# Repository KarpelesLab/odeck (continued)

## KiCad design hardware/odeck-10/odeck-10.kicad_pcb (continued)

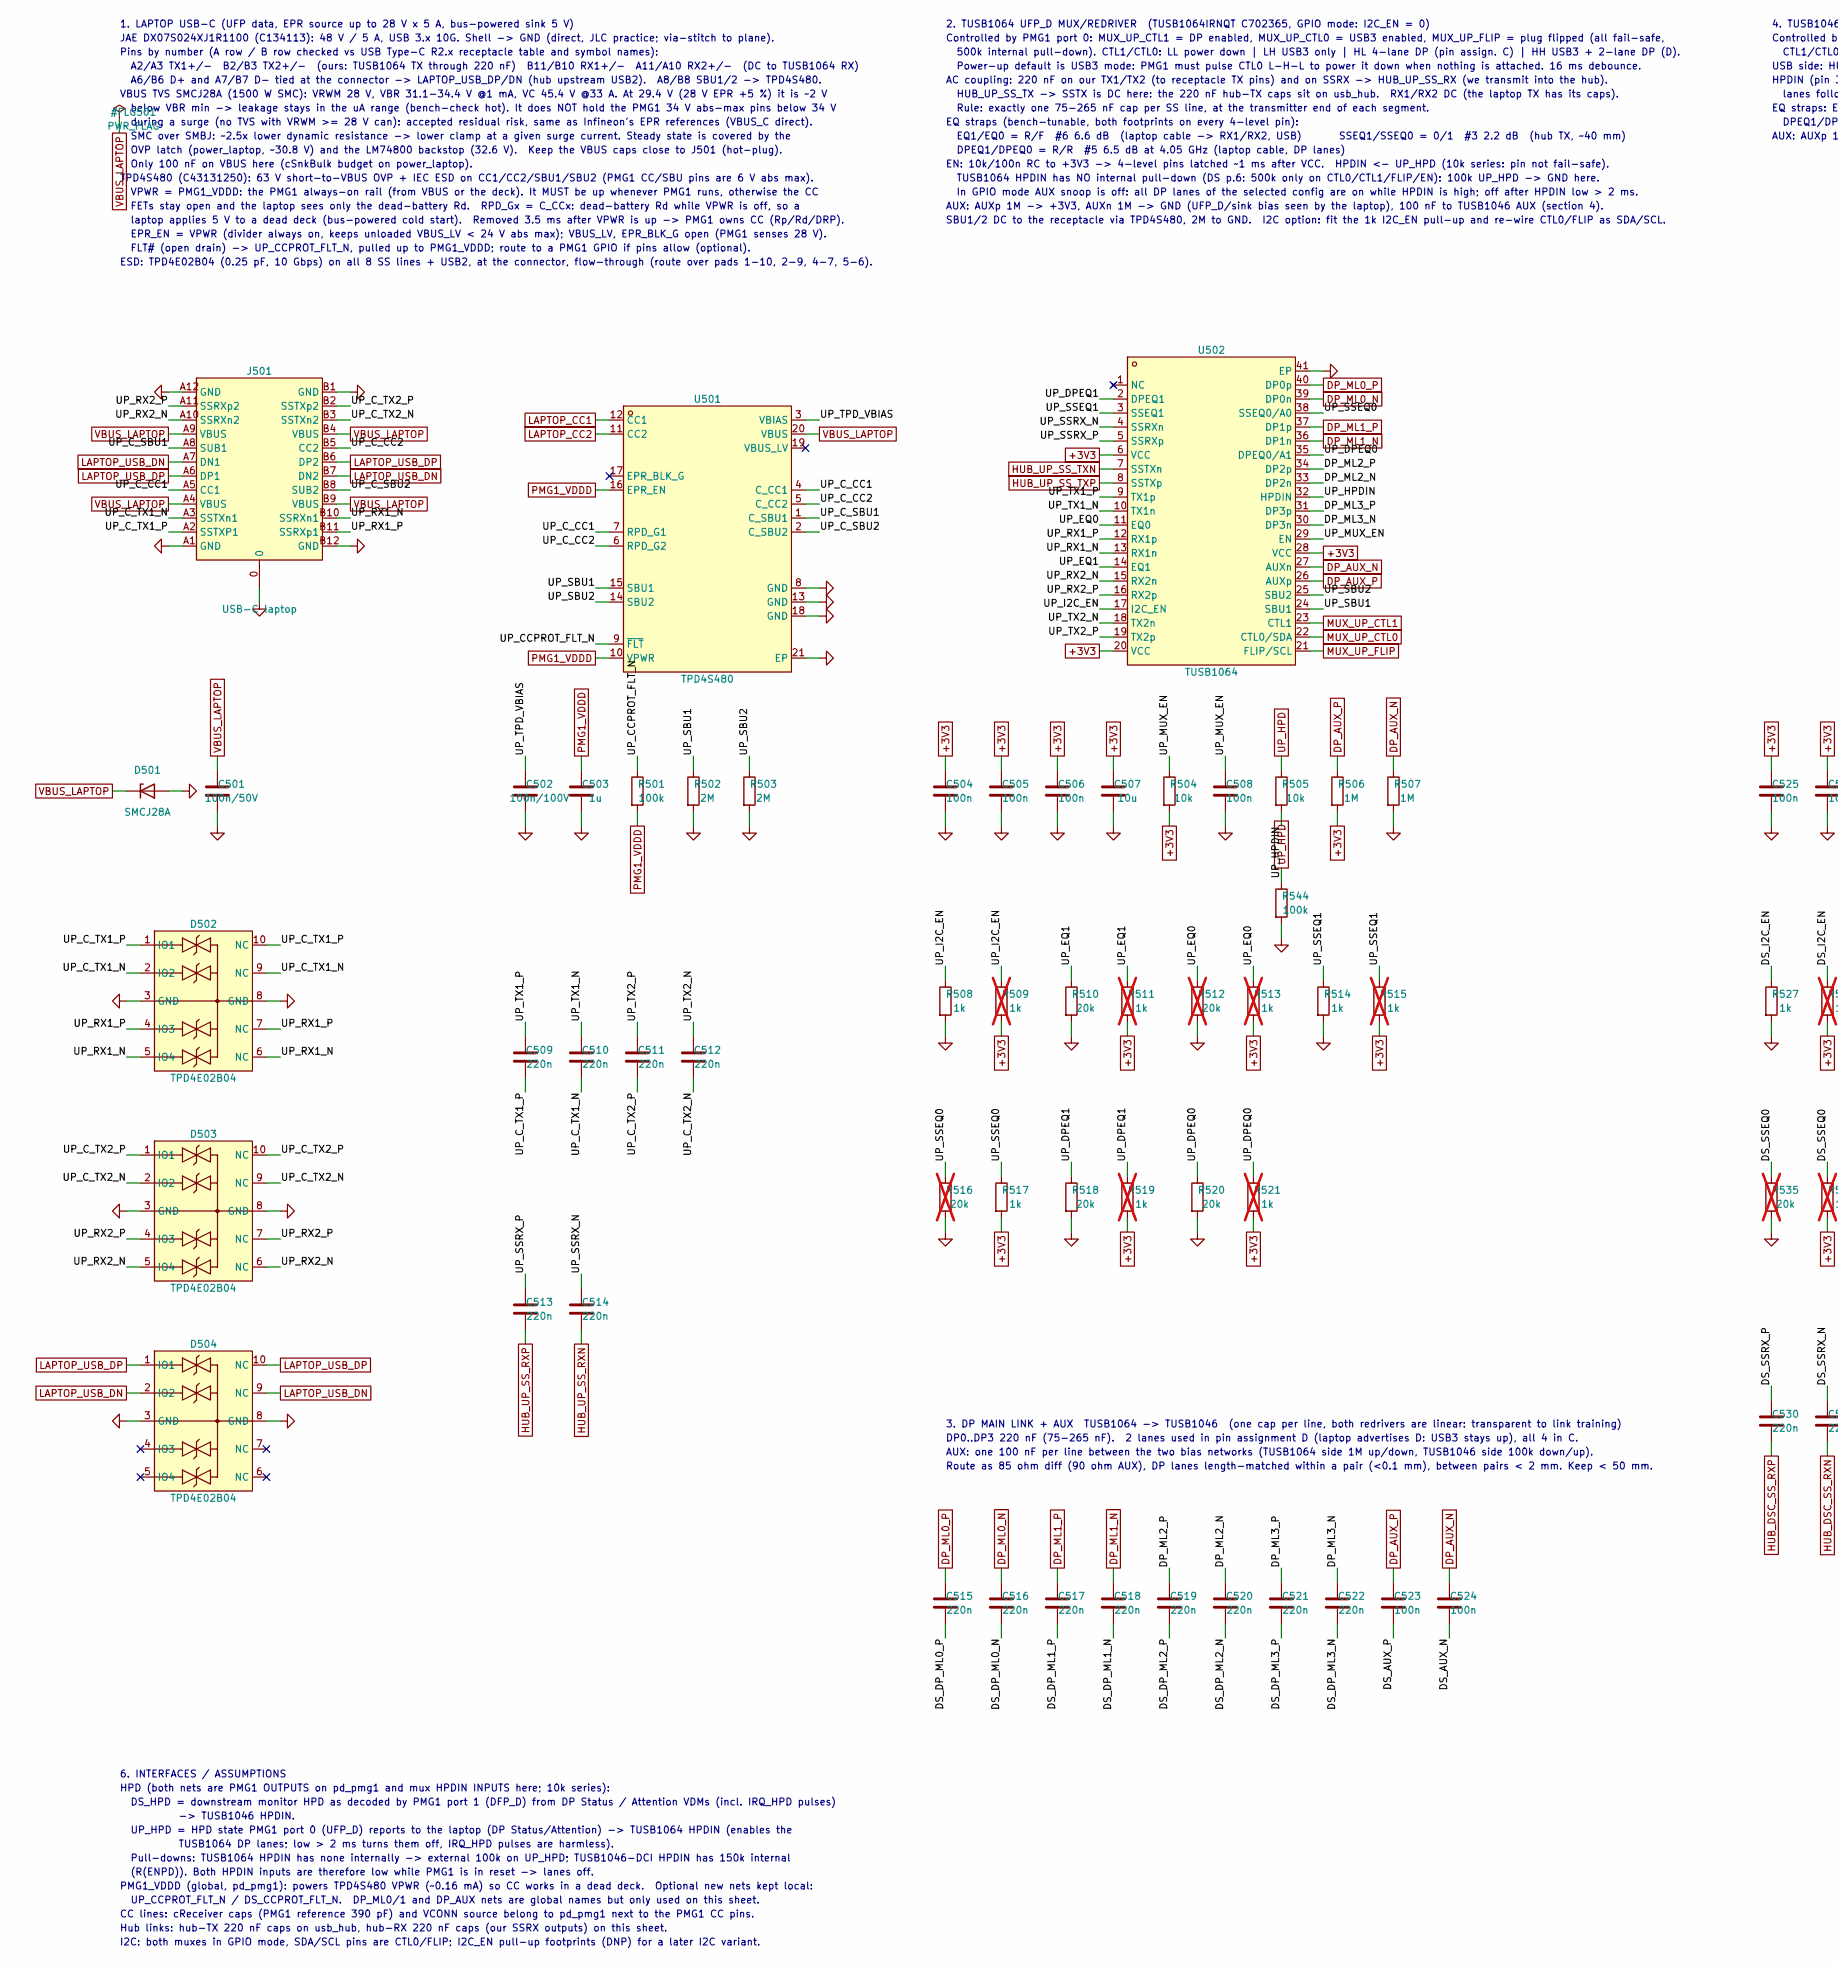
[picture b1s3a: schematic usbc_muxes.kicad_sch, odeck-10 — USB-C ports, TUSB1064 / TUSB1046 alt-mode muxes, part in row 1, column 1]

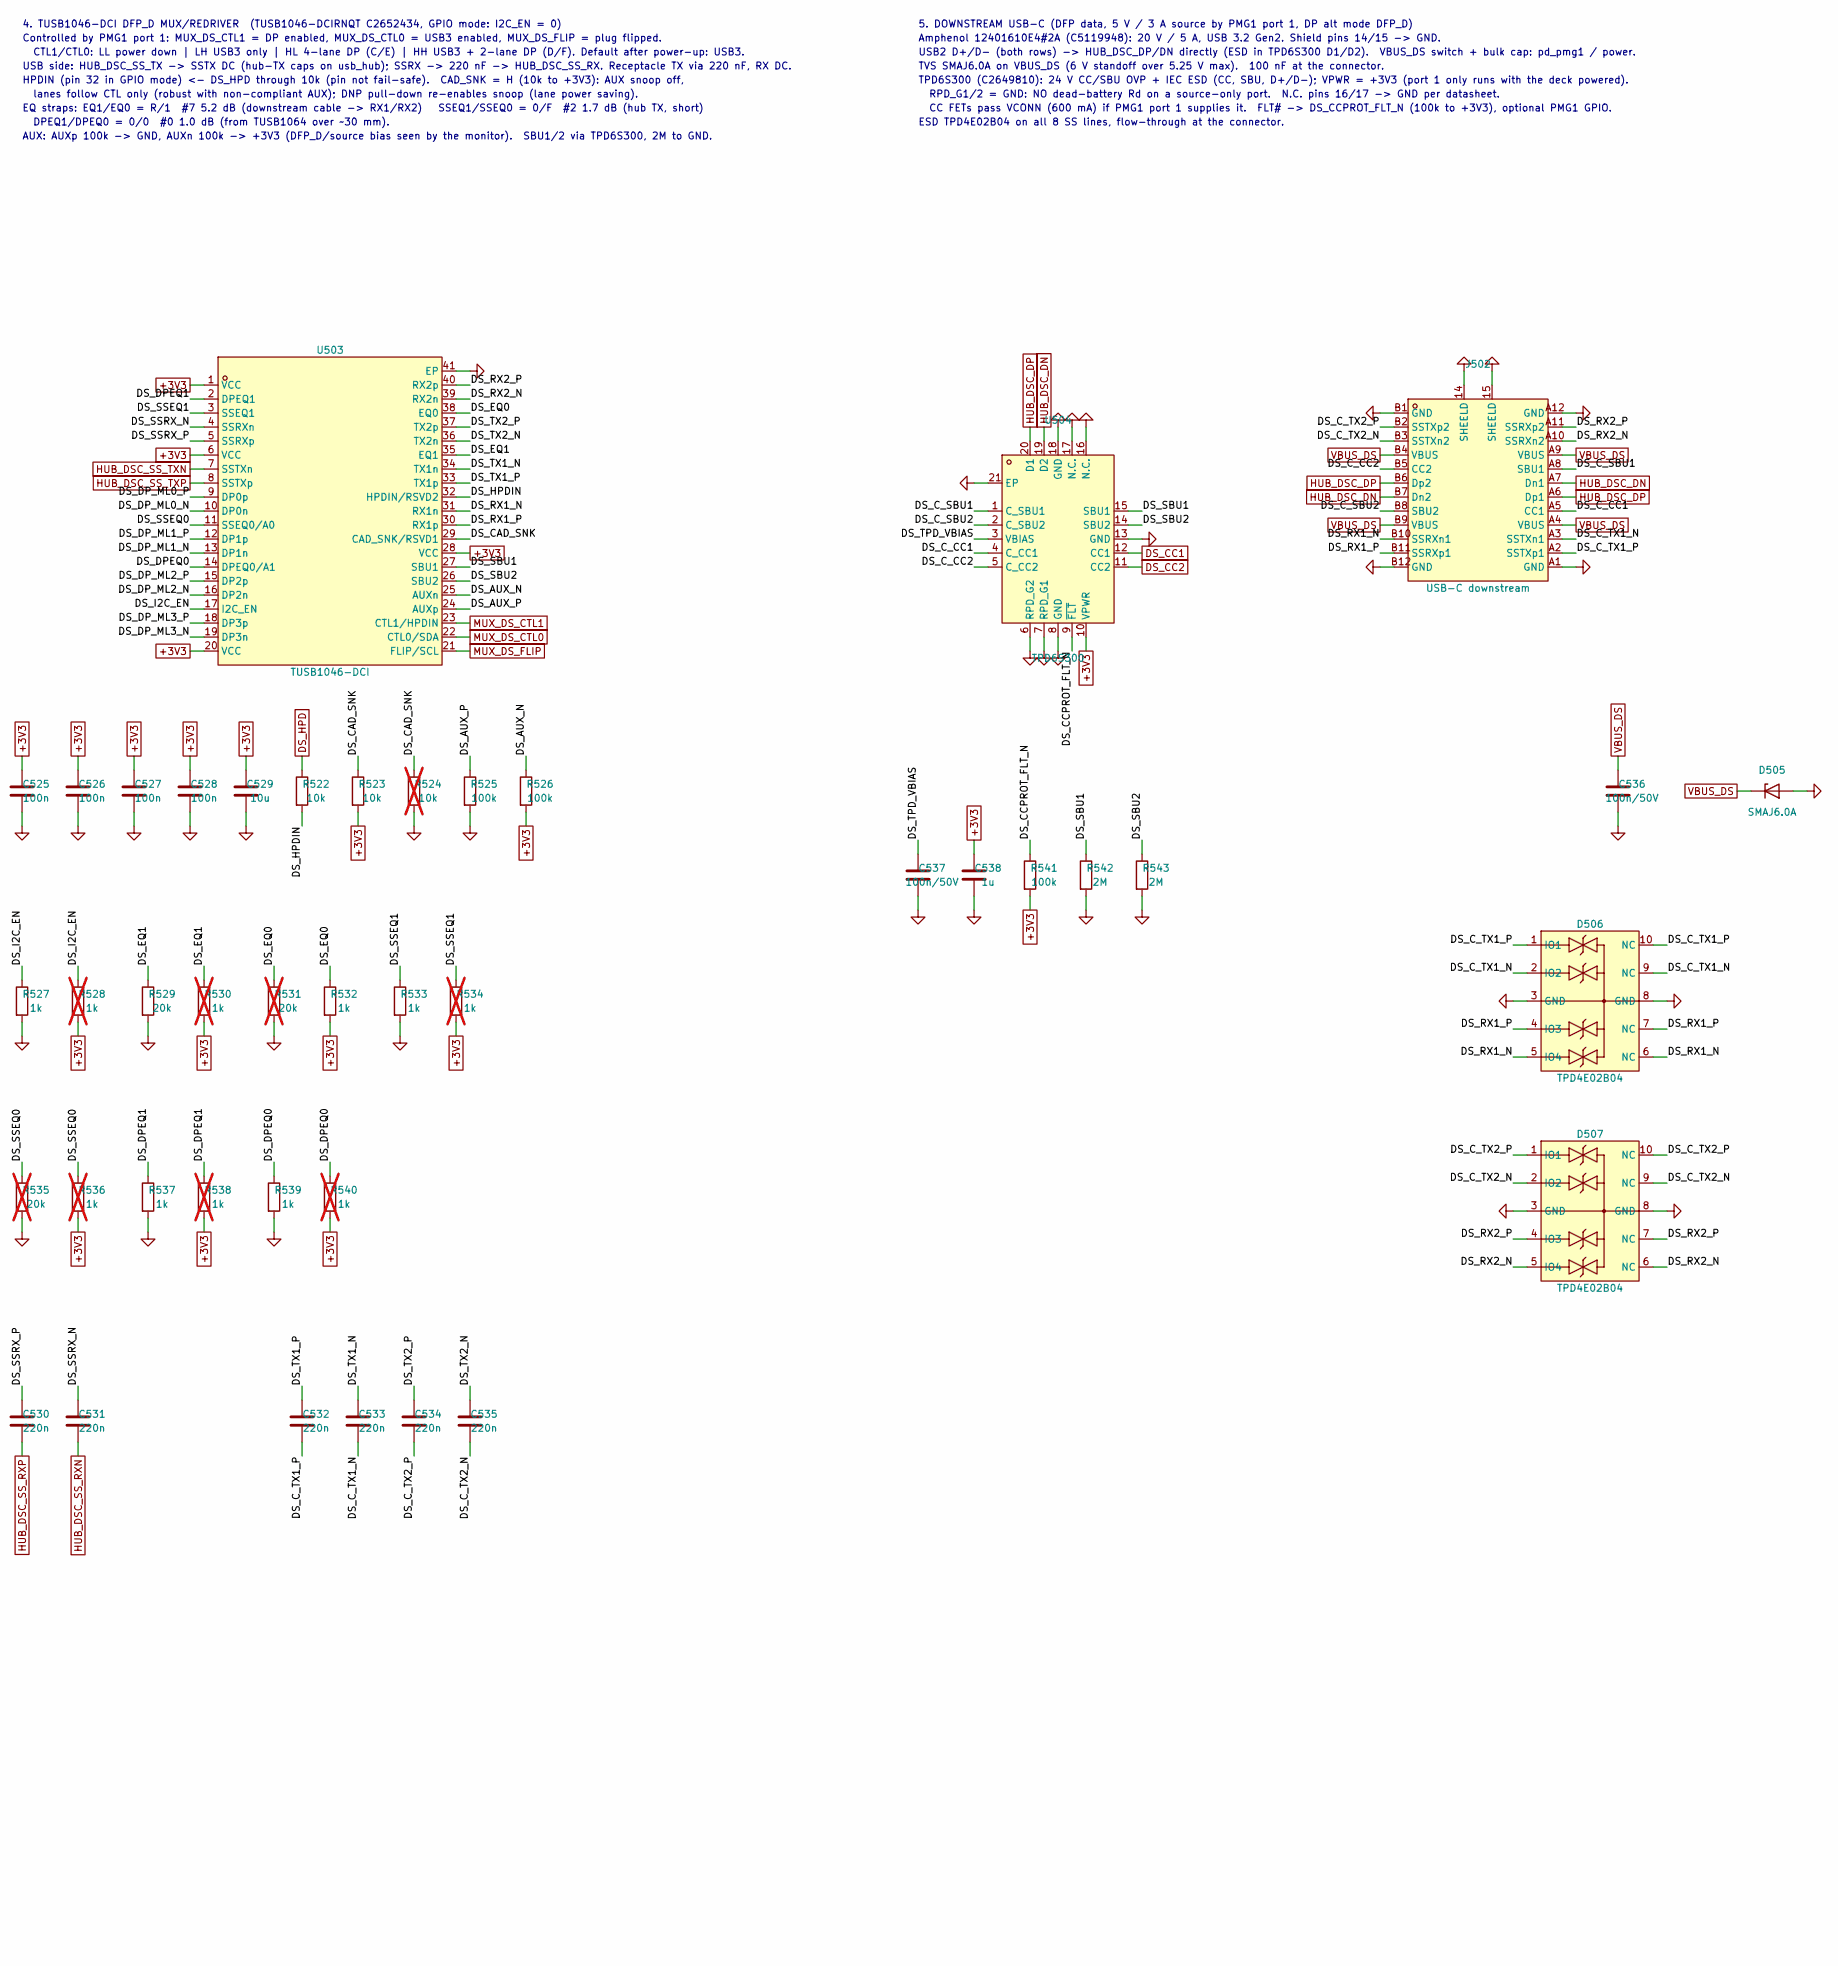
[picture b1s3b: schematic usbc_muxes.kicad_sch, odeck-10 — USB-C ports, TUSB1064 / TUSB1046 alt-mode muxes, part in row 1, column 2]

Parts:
C501, C536, C537: 100n/50V; C_0603_1608Metric; LCSC C14663
C502: 100n/100V; C_0805_2012Metric; LCSC C28233
C503, C538: 1u; C_0402_1005Metric; LCSC C52923
C504, C505, C506, C508, C523, C524, C525, C526, C527, C528: 100n; C_0402_1005Metric; LCSC C1525
C507, C529: 10u; C_0603_1608Metric; LCSC C19702
C509, C510, C511, C512, C513, C514, C515, C516, C517, C518, C519, C520, C521, C522, C530, C531, C532, C533, C534, C535: 220n; C_0402_1005Metric; LCSC C16772
D501: SMCJ28A; D_SMC; LCSC C224047
D502, D503, D504, D506, D507: TPD4E02B04; USON-10_L2.5-W1.0-P0.50-BL; MPN TPD4E02B04DQAR; LCSC C106794
D505: SMAJ6.0A; D_SMA; LCSC C364284
J501: USB-C laptop; USB-C-TH_DX07S024XJ1R1100-1; MPN DX07S024XJ1R1100; LCSC C134113
J502: USB-C downstream; USB-C-SMD_TYPE-C-24P; MPN 12401610E4#2A; LCSC C5119948
R501, R525, R526, R541, R544: 100k; R_0402_1005Metric; LCSC C25741
R502, R503, R542, R543: 2M; R_0603_1608Metric; LCSC C22976
R504, R505, R522, R523: 10k; R_0402_1005Metric; LCSC C25744
R506, R507: 1M; R_0402_1005Metric; LCSC C26083
R508, R514, R517, R527, R532, R533, R537, R539: 1k; R_0402_1005Metric; LCSC C11702
R509, R511, R513, R515, R519, R521, R528, R530, R534, R536, R538, R540: 1k; R_0402_1005Metric; LCSC C11702; not fitted
R510, R518, R520, R529: 20k; R_0402_1005Metric; LCSC C25765
R512, R516, R531, R535: 20k; R_0402_1005Metric; LCSC C25765; not fitted
R524: 10k; R_0402_1005Metric; LCSC C25744; not fitted
U501: TPD4S480; WQFN-20_L3.0-W3.0-P0.40-BL-EP1.7; MPN TPD4S480RUKR; LCSC C43131250
U502: TUSB1064; WQFN-40_L6.0-W4.0-P0.40-TL-EP; MPN TUSB1064IRNQT; LCSC C702365
U503: TUSB1046-DCI; WQFN-40_L6.0-W4.0-P0.40-TL-EP; MPN TUSB1046-DCIRNQT; LCSC C2652434
U504: TPD6S300; WQFN-20_L3.0-W3.0-P0.40-BL-EP1.7; MPN TPD6S300RUKR; LCSC C2649810

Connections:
+3V3: C504.1, C505.1, C506.1, C507.1, C525.1, C526.1, C527.1, C528.1, C529.1, C538.1, R504.2, R506.2, R509.2, R511.2, R513.2, R515.2, R517.2, R519.2, R521.2, R523.2, R526.2, R528.2, R530.2, R532.2, R534.2, R536.2, R538.2, R540.2, R541.2, U502.6 (VCC), U502.20 (VCC), U502.28 (VCC), U503.1 (VCC), U503.6 (VCC), U503.20 (VCC), U503.28 (VCC), U504.10 (VPWR); also elsewhere on the board
/USB-C muxes & DP/DP_ML2_N: C520.1, U502.33 (DP2n)
/USB-C muxes & DP/DP_ML2_P: C519.1, U502.34 (DP2p)
/USB-C muxes & DP/DP_ML3_N: C522.1, U502.30 (DP3n)
/USB-C muxes & DP/DP_ML3_P: C521.1, U502.31 (DP3p)
/USB-C muxes & DP/DS_AUX_N: C524.2, R526.1, U503.25 (AUXn)
/USB-C muxes & DP/DS_AUX_P: C523.2, R525.1, U503.24 (AUXp)
/USB-C muxes & DP/DS_CAD_SNK: R523.1, R524.1, U503.29 (CAD_SNK/RSVD1)
/USB-C muxes & DP/DS_CCPROT_FLT_N: R541.1, U504.9 (~FLT)
/USB-C muxes & DP/DS_C_CC1: J502.A5 (CC1), U504.4 (C_CC1)
/USB-C muxes & DP/DS_C_CC2: J502.B5 (CC2), U504.5 (C_CC2)
/USB-C muxes & DP/DS_C_SBU1: J502.A8 (SBU1), U504.1 (C_SBU1)
/USB-C muxes & DP/DS_C_SBU2: J502.B8 (SBU2), U504.2 (C_SBU2)
/USB-C muxes & DP/DS_C_TX1_N: C533.2, D506.2 (IO2), D506.9 (NC), J502.A3 (SSTXn1)
/USB-C muxes & DP/DS_C_TX1_P: C532.2, D506.1 (IO1), D506.10 (NC), J502.A2 (SSTXp1)
/USB-C muxes & DP/DS_C_TX2_N: C535.2, D507.2 (IO2), D507.9 (NC), J502.B3 (SSTXn2)
/USB-C muxes & DP/DS_C_TX2_P: C534.2, D507.1 (IO1), D507.10 (NC), J502.B2 (SSTXp2)
/USB-C muxes & DP/DS_DPEQ0: R539.1, R540.1, U503.14 (DPEQ0/A1)
/USB-C muxes & DP/DS_DPEQ1: R537.1, R538.1, U503.2 (DPEQ1)
/USB-C muxes & DP/DS_DP_ML0_N: C516.2, U503.10 (DP0n)
/USB-C muxes & DP/DS_DP_ML0_P: C515.2, U503.9 (DP0p)
/USB-C muxes & DP/DS_DP_ML1_N: C518.2, U503.13 (DP1n)
/USB-C muxes & DP/DS_DP_ML1_P: C517.2, U503.12 (DP1p)
/USB-C muxes & DP/DS_DP_ML2_N: C520.2, U503.16 (DP2n)
/USB-C muxes & DP/DS_DP_ML2_P: C519.2, U503.15 (DP2p)
/USB-C muxes & DP/DS_DP_ML3_N: C522.2, U503.19 (DP3n)
/USB-C muxes & DP/DS_DP_ML3_P: C521.2, U503.18 (DP3p)
/USB-C muxes & DP/DS_EQ0: R531.1, R532.1, U503.38 (EQ0)
/USB-C muxes & DP/DS_EQ1: R529.1, R530.1, U503.35 (EQ1)
/USB-C muxes & DP/DS_HPDIN: R522.2, U503.32 (HPDIN/RSVD2)
/USB-C muxes & DP/DS_I2C_EN: R527.1, R528.1, U503.17 (I2C_EN)
/USB-C muxes & DP/DS_RX1_N: D506.5 (IO4), D506.6 (NC), J502.B10 (SSRXn1), U503.31 (RX1n)
/USB-C muxes & DP/DS_RX1_P: D506.4 (IO3), D506.7 (NC), J502.B11 (SSRXp1), U503.30 (RX1p)
/USB-C muxes & DP/DS_RX2_N: D507.5 (IO4), D507.6 (NC), J502.A10 (SSRXn2), U503.39 (RX2n)
/USB-C muxes & DP/DS_RX2_P: D507.4 (IO3), D507.7 (NC), J502.A11 (SSRXp2), U503.40 (RX2p)
/USB-C muxes & DP/DS_SBU1: R542.1, U503.27 (SBU1), U504.15 (SBU1)
/USB-C muxes & DP/DS_SBU2: R543.1, U503.26 (SBU2), U504.14 (SBU2)
/USB-C muxes & DP/DS_SSEQ0: R535.1, R536.1, U503.11 (SSEQ0/A0)
/USB-C muxes & DP/DS_SSEQ1: R533.1, R534.1, U503.3 (SSEQ1)
/USB-C muxes & DP/DS_SSRX_N: C531.1, U503.4 (SSRXn)
/USB-C muxes & DP/DS_SSRX_P: C530.1, U503.5 (SSRXp)
/USB-C muxes & DP/DS_TPD_VBIAS: C537.1, U504.3 (VBIAS)
/USB-C muxes & DP/DS_TX1_N: C533.1, U503.34 (TX1n)
/USB-C muxes & DP/DS_TX1_P: C532.1, U503.33 (TX1p)
/USB-C muxes & DP/DS_TX2_N: C535.1, U503.36 (TX2n)
/USB-C muxes & DP/DS_TX2_P: C534.1, U503.37 (TX2p)
/USB-C muxes & DP/UP_CCPROT_FLT_N: R501.1, U501.9 (~FLT)
/USB-C muxes & DP/UP_C_CC1: J501.A5 (CC1), U501.4 (C_CC1), U501.7 (RPD_G1)
/USB-C muxes & DP/UP_C_CC2: J501.B5 (CC2), U501.5 (C_CC2), U501.6 (RPD_G2)
/USB-C muxes & DP/UP_C_SBU1: J501.A8 (SUB1), U501.1 (C_SBU1)
/USB-C muxes & DP/UP_C_SBU2: J501.B8 (SUB2), U501.2 (C_SBU2)
/USB-C muxes & DP/UP_C_TX1_N: C510.2, D502.2 (IO2), D502.9 (NC), J501.A3 (SSTXn1)
/USB-C muxes & DP/UP_C_TX1_P: C509.2, D502.1 (IO1), D502.10 (NC), J501.A2 (SSTXP1)
/USB-C muxes & DP/UP_C_TX2_N: C512.2, D503.2 (IO2), D503.9 (NC), J501.B3 (SSTXn2)
/USB-C muxes & DP/UP_C_TX2_P: C511.2, D503.1 (IO1), D503.10 (NC), J501.B2 (SSTXp2)
/USB-C muxes & DP/UP_DPEQ0: R520.1, R521.1, U502.35 (DPEQ0/A1)
/USB-C muxes & DP/UP_DPEQ1: R518.1, R519.1, U502.2 (DPEQ1)
/USB-C muxes & DP/UP_EQ0: R512.1, R513.1, U502.11 (EQ0)
/USB-C muxes & DP/UP_EQ1: R510.1, R511.1, U502.14 (EQ1)
/USB-C muxes & DP/UP_HPDIN: R505.2, U502.32 (HPDIN)
/USB-C muxes & DP/UP_I2C_EN: R508.1, R509.1, U502.17 (I2C_EN)
/USB-C muxes & DP/UP_MUX_EN: C508.1, R504.1, U502.29 (EN)
/USB-C muxes & DP/UP_RX1_N: D502.5 (IO4), D502.6 (NC), J501.B10 (SSRXn1), U502.13 (RX1n)
/USB-C muxes & DP/UP_RX1_P: D502.4 (IO3), D502.7 (NC), J501.B11 (SSRXp1), U502.12 (RX1p)
/USB-C muxes & DP/UP_RX2_N: D503.5 (IO4), D503.6 (NC), J501.A10 (SSRXn2), U502.15 (RX2n)
/USB-C muxes & DP/UP_RX2_P: D503.4 (IO3), D503.7 (NC), J501.A11 (SSRXp2), U502.16 (RX2p)
/USB-C muxes & DP/UP_SBU1: R502.1, U501.15 (SBU1), U502.24 (SBU1)
/USB-C muxes & DP/UP_SBU2: R503.1, U501.14 (SBU2), U502.25 (SBU2)
/USB-C muxes & DP/UP_SSEQ0: R516.1, R517.1, U502.38 (SSEQ0/A0)
/USB-C muxes & DP/UP_SSEQ1: R514.1, R515.1, U502.3 (SSEQ1)
/USB-C muxes & DP/UP_SSRX_N: C514.1, U502.4 (SSRXn)
/USB-C muxes & DP/UP_SSRX_P: C513.1, U502.5 (SSRXp)
/USB-C muxes & DP/UP_TPD_VBIAS: C502.1, U501.3 (VBIAS)
/USB-C muxes & DP/UP_TX1_N: C510.1, U502.10 (TX1n)
/USB-C muxes & DP/UP_TX1_P: C509.1, U502.9 (TX1p)
/USB-C muxes & DP/UP_TX2_N: C512.1, U502.18 (TX2n)
/USB-C muxes & DP/UP_TX2_P: C511.1, U502.19 (TX2p)
DP_AUX_N: C524.1, R507.1, U502.27 (AUXn)
DP_AUX_P: C523.1, R506.1, U502.26 (AUXp)
DP_ML0_N: C516.1, U502.39 (DP0n)
DP_ML0_P: C515.1, U502.40 (DP0p)
DP_ML1_N: C518.1, U502.36 (DP1n)
DP_ML1_P: C517.1, U502.37 (DP1p)
DS_CC1: U504.12 (CC1); also elsewhere on the board
DS_CC2: U504.11 (CC2); also elsewhere on the board
DS_HPD: R522.1; also elsewhere on the board
GND: C501.2, C502.2, C503.2, C504.2, C505.2, C506.2, C507.2, C508.2, C525.2, C526.2, C527.2, C528.2, C529.2, C536.2, C537.2, C538.2, D501.2 (A), D502.3 (GND), D502.8 (GND), D503.3 (GND), D503.8 (GND), D504.3 (GND), D504.8 (GND), D505.2 (A), D506.3 (GND), D506.8 (GND), D507.3 (GND), D507.8 (GND), J501.0, J501.A1 (GND), J501.A12 (GND), J501.B1 (GND), J501.B12 (GND), J502.14 (SHEELD), J502.15 (SHEELD), J502.A1 (GND), J502.A12 (GND), J502.B1 (GND), J502.B12 (GND), R502.2, R503.2, R507.2, R508.2, R510.2, R512.2, R514.2, R516.2, R518.2, R520.2, R524.2, R525.2, R527.2, R529.2, R531.2, R533.2, R535.2, R537.2, R539.2, R542.2, R543.2, R544.2, U501.8 (GND), U501.13 (GND), U501.18 (GND), U501.21 (EP), U502.41 (EP), U503.41 (EP), U504.6 (RPD_G2), U504.7 (RPD_G1), U504.8 (GND), U504.13 (GND), U504.16 (N.C.), U504.17 (N.C.), U504.18 (GND), U504.21 (EP); also elsewhere on the board
HUB_DSC_DN: J502.A7 (Dn1), J502.B7 (Dn2), U504.19 (D2); also elsewhere on the board
HUB_DSC_DP: J502.A6 (Dp1), J502.B6 (Dp2), U504.20 (D1); also elsewhere on the board
HUB_DSC_SS_RXN: C531.2; also elsewhere on the board
HUB_DSC_SS_RXP: C530.2; also elsewhere on the board
HUB_DSC_SS_TXN: U503.7 (SSTXn); also elsewhere on the board
HUB_DSC_SS_TXP: U503.8 (SSTXp); also elsewhere on the board
HUB_UP_SS_RXN: C514.2; also elsewhere on the board
HUB_UP_SS_RXP: C513.2; also elsewhere on the board
HUB_UP_SS_TXN: U502.7 (SSTXn); also elsewhere on the board
HUB_UP_SS_TXP: U502.8 (SSTXp); also elsewhere on the board
LAPTOP_CC1: U501.12 (CC1); also elsewhere on the board
LAPTOP_CC2: U501.11 (CC2); also elsewhere on the board
LAPTOP_USB_DN: D504.2 (IO2), D504.9 (NC), J501.A7 (DN1), J501.B7 (DN2); also elsewhere on the board
LAPTOP_USB_DP: D504.1 (IO1), D504.10 (NC), J501.A6 (DP1), J501.B6 (DP2); also elsewhere on the board
MUX_DS_CTL0: U503.22 (CTL0/SDA); also elsewhere on the board
MUX_DS_CTL1: U503.23 (CTL1/HPDIN); also elsewhere on the board
MUX_DS_FLIP: U503.21 (FLIP/SCL); also elsewhere on the board
MUX_UP_CTL0: U502.22 (CTL0/SDA); also elsewhere on the board
MUX_UP_CTL1: U502.23 (CTL1); also elsewhere on the board
MUX_UP_FLIP: U502.21 (FLIP/SCL); also elsewhere on the board
PMG1_VDDD: C503.1, R501.2, U501.10 (VPWR), U501.16 (EPR_EN); also elsewhere on the board
UP_HPD: R505.1, R544.1; also elsewhere on the board
VBUS_DS: C536.1, D505.1 (K), J502.A4 (VBUS), J502.A9 (VBUS), J502.B4 (VBUS), J502.B9 (VBUS); also elsewhere on the board
VBUS_LAPTOP: C501.1, D501.1 (K), J501.A4 (VBUS), J501.A9 (VBUS), J501.B4 (VBUS), J501.B9 (VBUS), U501.20 (VBUS); also elsewhere on the board

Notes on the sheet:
1. LAPTOP USB-C (UFP data, EPR source up to 28 V x 5 A, bus-powered sink 5 V)
JAE DX07S024XJ1R1100 (C134113): 48 V / 5 A, USB 3.x 10G. Shell -> GND (direct, JLC practice; via-stitch to plane).
Pins by number (A row / B row checked vs USB Type-C R2.x receptacle table and symbol names):
A2/A3 TX1+/- B2/B3 TX2+/- (ours: TUSB1064 TX through 220 nF) B11/B10 RX1+/- A11/A10 RX2+/- (DC to TUSB1064 RX)
A6/B6 D+ and A7/B7 D- tied at the connector -> LAPTOP_USB_DP/DN (hub upstream USB2). A8/B8 SBU1/2 -> TPD4S480.
VBUS TVS SMCJ28A (1500 W SMC): VRWM 28 V, VBR 31.1-34.4 V @1 mA, VC 45.4 V @33 A. At 29.4 V (28 V EPR +5 %) it is ~2 V
below VBR min -> leakage stays in the uA range (bench-check hot). It does NOT hold the PMG1 34 V abs-max pins below 34 V
during a surge (no TVS with VRWM >= 28 V can): accepted residual risk, same as Infineon's EPR references (VBUS_C direct).
SMC over SMBJ: ~2.5x lower dynamic resistance -> lower clamp at a given surge current. Steady state is covered by the
OVP latch (power_laptop, ~30.8 V) and the LM74800 backstop (32.6 V). Keep the VBUS caps close to J501 (hot-plug).
Only 100 nF on VBUS here (cSnkBulk budget on power_laptop).
TPD4S480 (C43131250): 63 V short-to-VBUS OVP + IEC ESD on CC1/CC2/SBU1/SBU2 (PMG1 CC/SBU pins are 6 V abs max).
VPWR = PMG1_VDDD: the PMG1 always-on rail (from VBUS or the deck). It MUST be up whenever PMG1 runs, otherwise the CC
FETs stay open and the laptop sees only the dead-battery Rd. RPD_Gx = C_CCx: dead-battery Rd while VPWR is off, so a
laptop applies 5 V to a dead deck (bus-powered cold start). Removed 3.5 ms after VPWR is up -> PMG1 owns CC (Rp/Rd/DRP).
EPR_EN = VPWR (divider always on, keeps unloaded VBUS_LV < 24 V abs max); VBUS_LV, EPR_BLK_G open (PMG1 senses 28 V).
FLT# (open drain) -> UP_CCPROT_FLT_N, pulled up to PMG1_VDDD; route to a PMG1 GPIO if pins allow (optional).
ESD: TPD4E02B04 (0.25 pF, 10 Gbps) on all 8 SS lines + USB2, at the connector, flow-through (route over pads 1-10, 2-9, 4-7, 5-6).
2. TUSB1064 UFP_D MUX/REDRIVER (TUSB1064IRNQT C702365, GPIO mode: I2C_EN = 0)
Controlled by PMG1 port 0: MUX_UP_CTL1 = DP enabled, MUX_UP_CTL0 = USB3 enabled, MUX_UP_FLIP = plug flipped (all fail-safe,
500k internal pull-down). CTL1/CTL0: LL power down | LH USB3 only | HL 4-lane DP (pin assign. C) | HH USB3 + 2-lane DP (D).
Power-up default is USB3 mode: PMG1 must pulse CTL0 L-H-L to power it down when nothing is attached. 16 ms debounce.
AC coupling: 220 nF on our TX1/TX2 (to receptacle TX pins) and on SSRX -> HUB_UP_SS_RX (we transmit into the hub).
HUB_UP_SS_TX -> SSTX is DC here: the 220 nF hub-TX caps sit on usb_hub. RX1/RX2 DC (the laptop TX has its caps).
Rule: exactly one 75-265 nF cap per SS line, at the transmitter end of each segment.
EQ straps (bench-tunable, both footprints on every 4-level pin):
EQ1/EQ0 = R/F #6 6.6 dB (laptop cable -> RX1/RX2, USB) SSEQ1/SSEQ0 = 0/1 #3 2.2 dB (hub TX, ~40 mm)
DPEQ1/DPEQ0 = R/R #5 6.5 dB at 4.05 GHz (laptop cable, DP lanes)
EN: 10k/100n RC to +3V3 -> 4-level pins latched ~1 ms after VCC. HPDIN <- UP_HPD (10k series: pin not fail-safe).
TUSB1064 HPDIN has NO internal pull-down (DS p.6: 500k only on CTL0/CTL1/FLIP/EN): 100k UP_HPD -> GND here.
In GPIO mode AUX snoop is off: all DP lanes of the selected config are on while HPDIN is high; off after HPDIN low > 2 ms.
AUX: AUXp 1M -> +3V3, AUXn 1M -> GND (UFP_D/sink bias seen by the laptop), 100 nF to TUSB1046 AUX (section 4).
SBU1/2 DC to the receptacle via TPD4S480, 2M to GND. I2C option: fit the 1k I2C_EN pull-up and re-wire CTL0/FLIP as SDA/SCL.
3. DP MAIN LINK + AUX TUSB1064 -> TUSB1046 (one cap per line, both redrivers are linear: transparent to link training)
DP0..DP3 220 nF (75-265 nF). 2 lanes used in pin assignment D (laptop advertises D: USB3 stays up), all 4 in C.
AUX: one 100 nF per line between the two bias networks (TUSB1064 side 1M up/down, TUSB1046 side 100k down/up).
Route as 85 ohm diff (90 ohm AUX), DP lanes length-matched within a pair (<0.1 mm), between pairs < 2 mm. Keep < 50 mm.
4. TUSB1046-DCI DFP_D MUX/REDRIVER (TUSB1046-DCIRNQT C2652434, GPIO mode: I2C_EN = 0)
Controlled by PMG1 port 1: MUX_DS_CTL1 = DP enabled, MUX_DS_CTL0 = USB3 enabled, MUX_DS_FLIP = plug flipped.
CTL1/CTL0: LL power down | LH USB3 only | HL 4-lane DP (C/E) | HH USB3 + 2-lane DP (D/F). Default after power-up: USB3.
